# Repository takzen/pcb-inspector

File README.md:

<div align="center">

# pcb-inspector

### *Automated Multimodal Design Reviewer & Linter for KiCad Projects*

Catch placement flaws, decoupling issues, routing problems, and mixed-signal design risks **before** sending your board to fabrication.

<p align="center">

</p>

[🎯 What is it?](#-what-is-it) • [⚡ Quickstart](#-quickstart--installation) • [📖 User Manual](MANUAL.md) • [🧠 Verification Pipeline](#-multi-layer-verification-pipeline) • [🤖 MCP Server & Agent Loop](#-mcp-server--agentic-integration) • [🏗️ Architecture](#️-design-philosophy) • [🚀 Use Cases](#-use-cases) • [🛠️ Roadmap](#️-roadmap--progress) • [📄 License](#-license)

---

</div>

> [!NOTE]
> **`pcb-inspector` v0.1.0 is now live!**  
> The 3-layer verification engine, built-in MCP server, interactive HTML reporting, and GitHub Action are fully functional. Check out the [📖 User Manual & Configuration Guide (MANUAL.md)](MANUAL.md) for practical examples, rule catalog, and per-project override guides.

## 🎯 What is it?

`pcb-inspector` is a multi-layer hardware verification and design-review pipeline for KiCad projects.

Traditional DRC/ERC tools are essential, but they primarily verify explicit electrical and geometric rules. `pcb-inspector` adds higher-level **layout analysis, engineering heuristics, and multimodal visual review** to identify potential design issues that may pass standard CAD checks.

It can run standalone as a **CLI or GitHub Action** on manually designed boards, or integrate with agentic PCB workflows such as **Konnect** to create a closed-loop design → audit → fix → verify workflow.

> [!TIP]
> **Don't just generate a PCB. Independently inspect it before you manufacture it.**  
> *Design. Inspect. Fix. Verify.*

---

## ⚡ Quickstart & Installation

### Installation

```bash
# Using uv (recommended)
uv pip install pcb-inspector

# Or install from source
uv pip install "git+https://github.com/takzen/pcb-inspector.git"

# Optional: Claude (Fable / Opus) as the vision model
uv pip install "pcb-inspector[claude]"
```

> [!IMPORTANT]
> Layer 1 (DRC/ERC) and hosted vision renders both need **KiCad 8+** with `kicad-cli` on `PATH`
> (or `kicad_cli_path` in the config). Without it, Layer 1 is reported as **not run** rather than
> silently skipped; pass `--require-kicad-cli` to make that a failure, as the bundled GitHub
> Action does.

### Essential CLI Commands

```bash
# 1. Full 3-layer audit (DRC + Heuristics + Vision) with interactive HTML report
pcb-inspector check path/to/board.kicad_pcb -o report.html -f html

# 2. Fast deterministic DRC/ERC only (native KiCad)
pcb-inspector drc path/to/board.kicad_pcb

# 3. Spatial & physical engineering heuristics only
pcb-inspector analyze path/to/board.kicad_pcb

# 4. Dedicated Multimodal AI Vision Review (Gemini Flash 3.8, Fable 5, GPT-6 Astra)
pcb-inspector vision path/to/board.kicad_pcb --model gemini-3.8-flash

# 5. Continuous Watch Mode (automatically re-checks on board save)
pcb-inspector check path/to/board.kicad_pcb --watch

# 6. Launch Model Context Protocol (MCP) server for AI agents
pcb-inspector mcp --transport stdio
```

---

## 🧠 Multi-Layer Verification Pipeline

`pcb-inspector` approaches design verification through three complementary layers of defense:

```mermaid
flowchart TD
    subgraph Input ["📥 Design Input"]
        SCH["📄 Schematic Files (.kicad_sch)"]
        PCB["📐 PCB Layout (.kicad_pcb)"]
    end

    subgraph Pipeline ["🔍 pcb-inspector Verification Engine"]
        direction TB
        L1["1️⃣ Deterministic Ground Truth<br/><code>kicad-cli</code> (ERC & DRC checks)"]
        L2["2️⃣ Programmatic Engineering Heuristics<br/>(Decoupling, loop areas, return paths)"]
        L3["3️⃣ Multimodal Visual Review<br/>(Vision LLM on 2D/3D renders)"]
        
        L1 --> Aggregator
        L2 --> Aggregator
        L3 --> Aggregator
        Aggregator["⚡ Findings Aggregator & Prioritizer"]
    end

    subgraph Output ["📋 Actionable Report"]
        Report["🔴 CRITICAL • 🟠 WARNING • 🟡 SUGGESTION • 🟢 PASS<br/>Coordinates • Net Names • Evidence • Fix Instructions"]
    end

    Input --> Pipeline
    Aggregator --> Output
```

### 1. Deterministic Ground Truth
Runs KiCad's native verification tools through `kicad-cli`:
- **ERC** — Electrical Rules Check
- **DRC** — Design Rules Check
- Connectivity & netlist verification, including schematic parity: footprints missing from
  or extra on the board and pads on the wrong net, grouped by kind
- Clearance and short-circuit detection
- Unconnected pins and nets
- Manufacturing and fabrication constraint violations

*These results form the deterministic baseline for the entire audit.*

---

### 2. Programmatic Design Analysis
Five rules computed directly from the layout, reading the design intent KiCad records: net classes
from the `.kicad_pro`, the copper stack order, and each pad's schematic pin name.

- **Decoupling capacitor placement** (`HEUR-DEC-001`) — distance from every IC supply pin to its
  nearest bypass capacitor, adding the board thickness for capacitors on the opposite side. Supply
  pins are recognised by their schematic pin name (`VDD`, `VCC`, `3.3V`, `+VS`…) as well as the
  net name; a bias or reference net such as `BIAS_1.65V` is not mistaken for a rail.
- **Power rail trace width** (`HEUR-PWR-001`) — one finding per net and layer. A trace narrower
  than **its own net class** is a warning; one that matches its net class but sits below the
  configured power-rail guideline is a suggestion, since KiCad treats net class widths as defaults.
- **Differential pair skew** (`HEUR-DIFF-001`) — length mismatch across `_P/_N`, `+/-`,
  `_DP/_DM` and `H/L` pairs, counting curved (arc) routing and via transitions. Only pairs named
  as a fast interface (USB, HDMI, PCIe, LVDS, Ethernet, clocks…) can be critical; a CAN bus or an
  analog sensor pair is a suggestion, since millimetres of skew are picoseconds.
- **Switching regulator loop area** (`HEUR-DCDC-001`) — switching nodes confirmed by a declared
  `SW`/`LX` pin or by inductor-to-converter topology, never by net name alone.
- **Ground reference** (`HEUR-GND-001`) — the share of each signal segment lying over a ground
  plane on an **adjacent** copper layer, read from the board's physical stack order.

> [!NOTE]
> Thresholds are configurable globally and per rule via `custom_rules` in YAML; any rule can be
> disabled there. See [MANUAL.md](MANUAL.md) for every key.

Not yet implemented, and listed in the [Roadmap](#️-roadmap--progress): thermal proximity of
heat-sensitive parts to hot spots, analog/digital separation, copper-weight and via current
capacity, and star-routing checks.

---

### 3. Multimodal Visual Review
Each side of the board is raytraced to PNG with `kicad-cli pcb render` and reviewed in its own
request by Gemini, OpenAI or Claude (Fable/Opus). The API key is read from the chosen provider's
own variable — `GOOGLE_API_KEY` or `GEMINI_API_KEY`, `OPENAI_API_KEY` or `ANTHROPIC_API_KEY` —
exported or kept in a `.env` file in the directory you run from; use `--vision-model mock` to
run offline. A spent daily quota is reported at once rather than retried. Hosted models need the `kicad-cli` render; the tool refuses to send them anything
else rather than fail at the provider. Vision models catch layout anti-patterns that resist
formulation into rigid CAD rules:
- **Component placement:** Clustering balance, awkward orientations, and assembly congestion.
- **Routing aesthetics & quality:** Unnecessary detours, awkward acute angles, and excessive vias.
- **Silkscreen & DFM:** Overlapping silkscreens, unreadable reference designators, and obstructed testpoints.
- **Polarity & Pin 1:** Missing or ambiguous diode/electrolytic polarity and IC Pin 1 indicators.
- **Mechanical fit:** Edge clearance, mounting hole keepouts, and connector access clearances.
- **Schematic intent vs. PCB:** Visual cross-check ensuring physical layout reflects functional schematic grouping.

*Vision review acts as an automated "peer engineer over your shoulder" — probabilistic guidance backed by deterministic verification.*

---

### 4. Structured, Actionable Feedback
Produces a clean, prioritized report tailored for both human review and automated agent consumption:

| Severity | Meaning | Example |
| :--- | :--- | :--- |
| 🔴 **`CRITICAL`** | Functional failure or manufacturing blocker | DRC short, bypass capacitor on wrong side of via |
| 🟠 **`WARNING`** | Signal integrity, thermal, or EMI hazard | High-speed trace crossing ground slot, undersized power trace |
| 🟡 **`SUGGESTION`** | DFM, readability, or best-practice refinement | Obscured silkscreen, sub-optimal component rotation |
| 🟢 **`PASS`** | Clean verification | All power rails decoupled within target metrics |

Each finding includes:
- Component designators (e.g., `U1`, `C14`, `L2`)
- Affected nets & physical PCB coordinates $(X, Y)$
- Measured values vs. expected thresholds
- Visual snapshots / highlighted bounding boxes
- Concrete, actionable remediation instructions

---

## 🤖 MCP Server & Agentic Integration

`pcb-inspector` provides a native **Model Context Protocol (MCP)** server, making it a drop-in verification tool for AI coding and design agents (Claude Desktop, Cursor, Antigravity).

### 🤝 The Dual-MCP Synergy: `Konnect` + `pcb-inspector`

In modern autonomous hardware workflows, agents need both **actuators** (to edit KiCad designs) and **sensors/auditors** (to verify physical correctness):

| Role | MCP Server | Function |
| :--- | :--- | :--- |
| **The Hands (Actuator)** | **`Konnect`** *(by mixelpixx)* | Adds components, connects pins, routes traces, modifies footprints in KiCad. |
| **The Brain & Eyes (Auditor)** | **`pcb-inspector`** *(this project)* | Validates DRC/ERC, decoupling proximity, switching loops, ground cuts, and silkscreen DFM. |

Together, they enable a **closed-loop autonomous self-correction loop**:

```mermaid
sequenceDiagram
    autonumber
    participant Agent as 🤖 Autonomous Agent (Claude / Cursor)
    participant Konnect as 🖐️ Konnect MCP (KiCad Actuator)
    participant Project as 📁 KiCad Project (.kicad_pcb)
    participant Inspector as 👁️ pcb-inspector MCP (Auditor)
    participant Fab as 🏭 Fabrication (JLCPCB / PCBWay)

    Agent->>Konnect: place_component / route_track
    Konnect->>Project: Edits the board live in KiCad (IPC API, undoable)
    Agent->>Inspector: call tool `inspect_project(live=true)`
    activate Inspector
    Inspector->>Project: Snapshot of the open board, then DRC + Heuristics + Vision
    Inspector-->>Agent: Returns structured JSON findings + coordinates
    deactivate Inspector

    alt Violations Found (e.g. Decoupling too far, DRC clearance)
        Agent->>Konnect: Move C3 closer (< 3.5mm), dry run first, reroute track
        Note over Agent,Inspector: Agent automatically iterates until 🟢 PASS
    else All Checks Pass (🟢 PASS)
        Agent->>Fab: Export Gerbers & send to production!
    end
```

Konnect edits the board in the running KiCad; the file on disk changes only when someone
saves. The audit step therefore reads the **open board** with `live=true` (or `--live` on the
CLI), unsaved edits included, through KiCad's API. It needs `pip install 'pcb-inspector[live]'`
and *Preferences → Plugins → Enable KiCad API* in KiCad 10. Konnect's own plans are worth
auditing before they are applied: on a real board its `place_decoupling_caps` dry run for one
op-amp gathered every capacitor sharing ground, scoring itself 70 → 10.

### 🛠️ Exposed MCP Tools

When launched with `pcb-inspector mcp`, the server provides:

- `inspect_project(project_path: str = "", live: bool = False)`: Runs the complete 3-layer audit (DRC, Heuristics, Vision) and returns prioritized findings. Every tool takes `live=true` in place of a path.
- `check_decoupling(pcb_path: str, max_distance_mm: float = 3.5)`: Rapid spatial analysis of IC power pins and decoupling bypass capacitors.
- `run_drc(pcb_path: str)`: Fast deterministic DRC check returning structured clearance and connectivity violations.
- `get_actionable_fixes(project_path: str)`: Machine-readable $(X, Y)$ coordinate patches and step-by-step remediation commands for agents.

---

## 🏗️ Design Philosophy

`pcb-inspector` enforces a strict separation of concerns across its verification tiers:

| Layer | Purpose | Authority | Predictability |
| :--- | :--- | :--- | :--- |
| **KiCad DRC/ERC** | Explicit electrical & geometric constraints | Deterministic | Exact |
| **Programmatic Analysis** | Measurable engineering heuristics & physics | Deterministic / Configurable | High |
| **Vision Review** | Spatial sanity, aesthetics & assembly review | Probabilistic | Heuristic |

> [!IMPORTANT]
> No single layer catches everything. By stacking deterministic CAD checks with spatial analytics and visual AI, `pcb-inspector` achieves coverage that standard DRC cannot match.

---

## 🚀 Use Cases

- 🤖 **AI-Generated PCB Designs:** Autonomous validation for LLM/agent-designed boards.
- ⚡ **Mixed-Signal & Audio:** Protecting analog front-ends from noisy digital microcontrollers.
- 🔋 **Power Electronics:** Verifying DC/DC buck/boost switching loops and thermal copper pours.
- 📡 **RF & High-Speed Digital:** Return paths, differential pair continuity, and keepout verification.
- ⏱️ **Pre-Fabrication Sanity Check:** Catching Silkscreen, footprint, and assembly bugs before purchasing silicon.
- 🔄 **CI/CD for Hardware:** Automated regression testing on every Git pull request.

---

## 🛠️ Roadmap & Progress

### v0.1.0 (Released)
- [x] Three-tier verification architecture design & domain data models
- [x] KiCad 8 / 9 / 10 CLI automation wrappers (`kicad-cli`) & DRC/ERC JSON parsers
- [x] Programmatic spatial & physical heuristics (decoupling, DC/DC loops, return paths, diff pairs, power traces)
- [x] Multimodal vision inspection engine (Gemini Flash 3.8, Fable 5, GPT-6 Astra)
- [x] Board renderer for vision review (superseded — see Unreleased)
- [x] Built-in Model Context Protocol (MCP) Server (`pcb-inspector mcp`) for autonomous agent loops
- [x] Konnect agentic closed-loop integration & `ActionableFix` auto-repair coordinates
- [x] Continuous watch mode (`--watch`) for real-time iterative layout reviews
- [x] Multi-format reporting: Interactive HTML5 (zero CDN), Markdown, JSON, and Terminal Rich
- [x] Reusable GitHub Action (`.github/actions/pcb-inspector`) for CI/CD pipelines
- [x] Golden Sample reference benchmark boards (`clean_board` & `flawed_board`)

### Unreleased — reliability and accuracy
- [x] Live audits of the board open in KiCad 10 (`--live`, MCP `live=true`), so a repair loop
  driven through Konnect sees its own unsaved edits
- [x] Vision reads its API key from `.env` too, accepts `GOOGLE_API_KEY` as Google's own tools
  do, and stops retrying once a daily quota is spent (verified against the live Gemini API)
- [x] Checked against a real KiCad 10 analog board: the CLI no longer crashes on ERC titles
  such as `ERC [/]:`, supply rails are recognised the same way by every rule (`+3.3V` was
  missed, `BIAS_1.65V` was taken for one), and DRC checks schematic parity
- [x] A target holding no board or schematic is a usage error (exit 2), no longer a PASSED
  audit with a 100/100 health score; the MCP tools return an error for it too
- [x] Never report a clean board for work not done: failed or missing `kicad-cli` is a finding,
  every run records which layers executed, and the GitHub Action installs KiCad
- [x] Parser reads the KiCad 10 file format (nets named inline), curved (arc) tracks,
  multi-layer zones, net classes, the layer stack and pad
  pin names; pad positions match `pcbnew` exactly
- [x] Heuristics fixed for false positives on connectors, SWD/PHY nets and matched pairs, with
  repair actions keyed to the rule that produced them
- [x] Vision review works with hosted models: raytraced PNG per side via `kicad-cli pcb render`,
  Claude through the Anthropic SDK with refusal fallbacks, Gemini requests reach the configured
  model instead of being rewritten to `gemini-2.0-flash`
- [x] Findings correlation, ground-reference check and watch mode made fast enough for
  26,000-track boards
- [x] HTML report search and category filtering; smoke tests over KiCad's own demo boards

### Future Enhancements (v0.2.0+)
- [ ] Thermal rule: heat-sensitive parts near power dissipation hot spots
- [ ] Analog/digital separation: analog traces crossing digital buses or plane splits
- [ ] Via current capacity and copper-weight-aware trace width
- [ ] Star-routing and ground-split checks
- [ ] Direct Gerber (RS-274X) & Excellon drill file fabrication inspection
- [ ] Automated IPC-2221 conductor spacing & current-carrying capacity calculator
- [ ] Differential TDR waveform simulation for transmission lines

---

## ⚠️ Engineering Disclaimer

`pcb-inspector` is an automated design-review tool, not a substitute for professional engineering certification. Vision models and heuristic checks may yield false positives or overlook specific corner-case failure modes. Final sign-off and safety-critical decisions remain the sole responsibility of the engineer.

---

## 📄 License & Author

This project is licensed under the **MIT License** — see the [LICENSE](LICENSE) file for complete details.

**Author & Maintainer:**  
👤 **Krzysztof Pika** ([@takzen](https://github.com/takzen))  
📫 Contact: [takzen.app@gmail.com](mailto:takzen.app@gmail.com)

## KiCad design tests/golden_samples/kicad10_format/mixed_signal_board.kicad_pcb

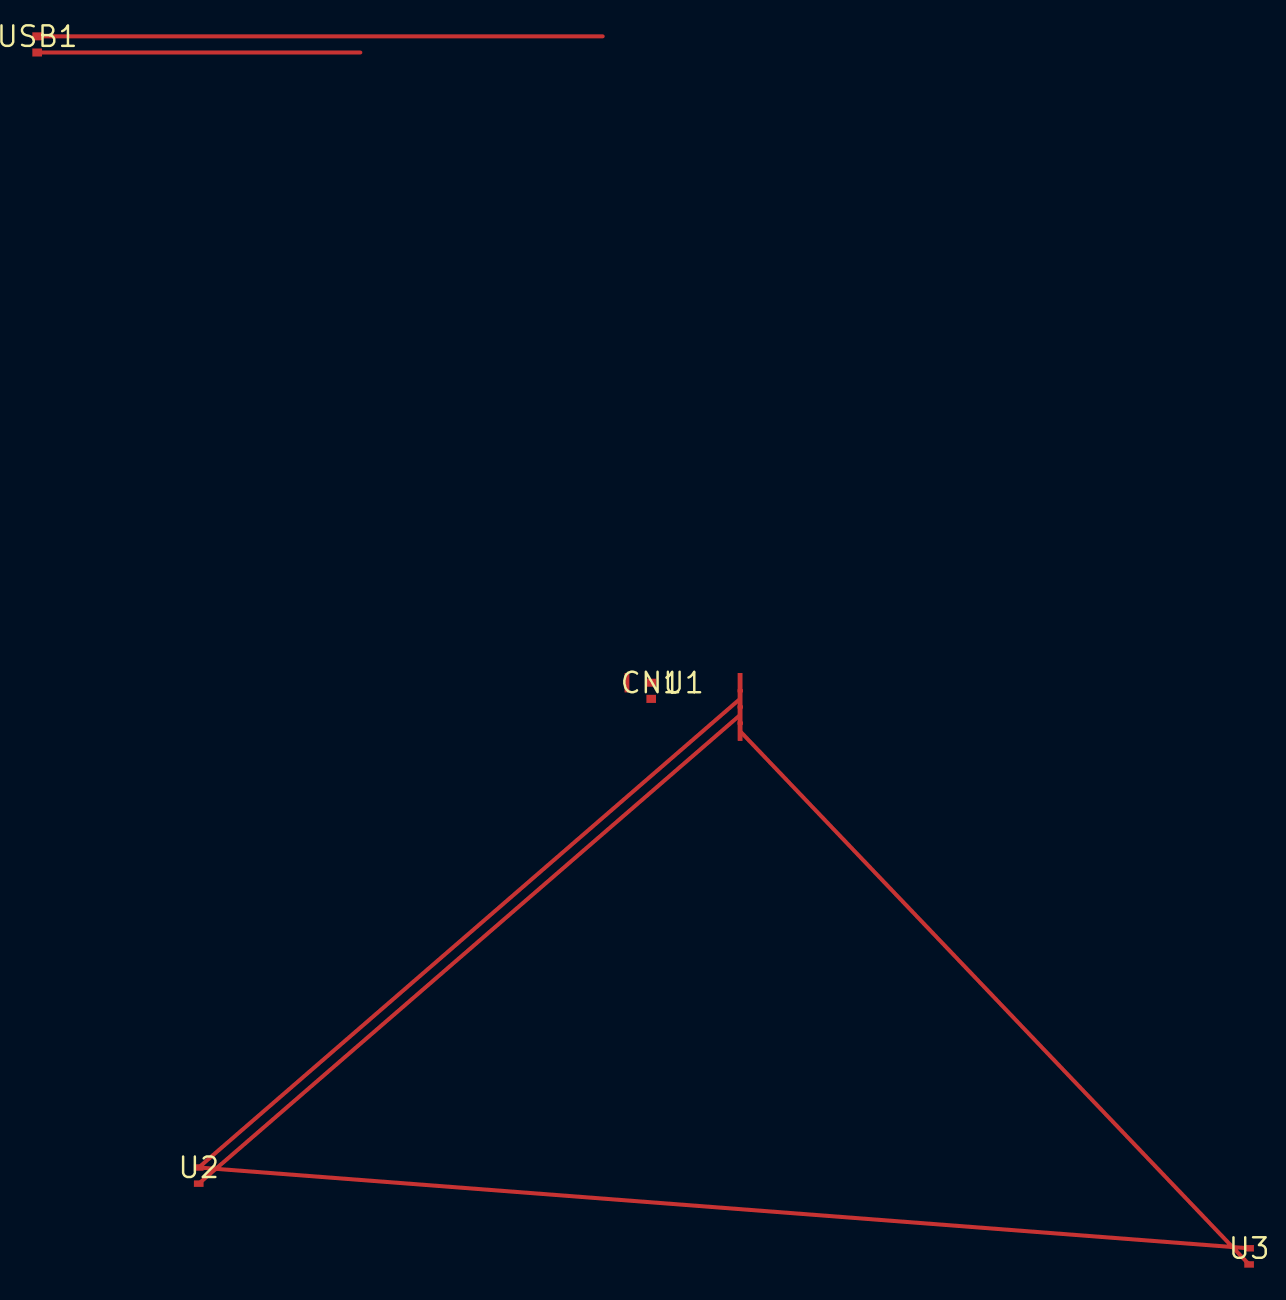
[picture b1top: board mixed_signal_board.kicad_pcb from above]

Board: 2 copper layers, 5 parts (0 on the bottom side), 5 nets.

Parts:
CN1: DebugHeader; Conn_01x04
U1: STM32F401; LQFP-48
U2: DebugBuffer; SOT-23
U3: LevelShifter; SOT-23
USB1: USB-C; USB_C_Receptacle

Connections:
+3V3: CN1.1, U1.1 (VDD)
GND: CN1.2, U1.2 (VSS)
PHY_TXD: U1.5, U3.2
SWCLK: U1.3, U2.1, U3.1
SWDIO: U1.4, U2.2

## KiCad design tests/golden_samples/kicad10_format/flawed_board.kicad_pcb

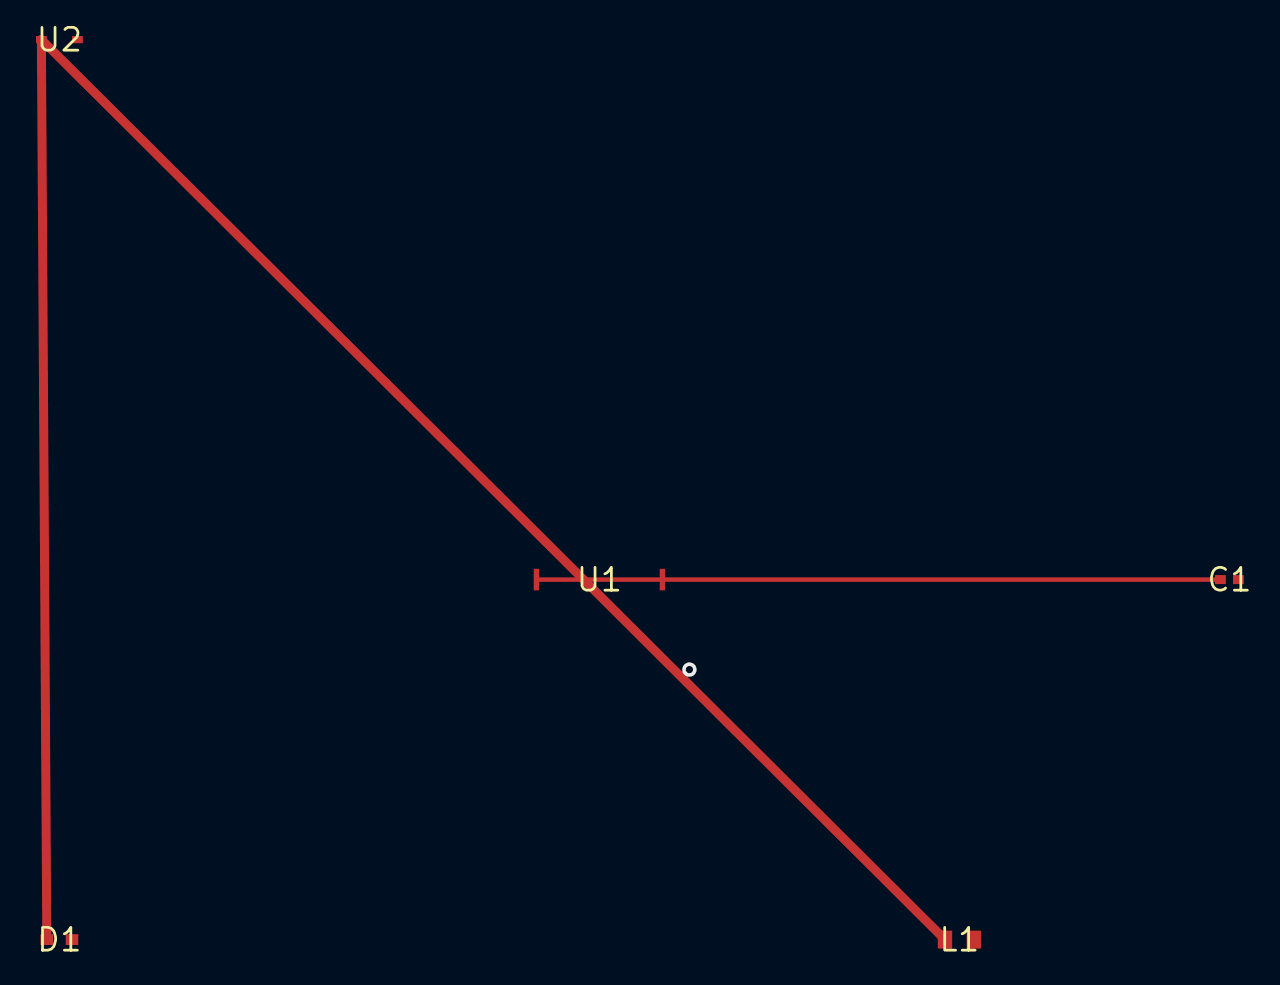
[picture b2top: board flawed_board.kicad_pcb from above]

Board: 2 copper layers, 5 parts (0 on the bottom side), 3 nets.

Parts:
C1: 100nF; C_0402_1005Metric
D1: B0540W; D_SOD-323
L1: 2.2uH; L_0805_2012Metric
U1: STM32F401; LQFP-48
U2: TPS62170; SOT-23-6

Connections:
+3V3: C1.1, L1.2, U1.1 (VDD)
GND: C1.2, D1.2, U1.2 (VSS), U2.2 (GND)
SW: D1.1, L1.1, U2.1 (SW)

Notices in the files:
README.md:
License: MIT
